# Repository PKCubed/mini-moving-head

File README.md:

# Mini Moving Head

This project aims to create a miniature moving head light fixture for my miniature stage. This fixture needs to have motorized pan and tilt, and should have a bright LED with a collimating lens to create as tight of a beam as possible. For now, a single color LED is acceptable due to the size constraints, as a multicolor LED with individual separate LED dies in side the package causes individual colored beams preventing color mixing.

This project consists of a custom circuit board with an RP2040 on board to take in unbalanced "DMX" signals from the "DMX" bus and read channel data for it's pan and tilt position and the brightness of it's LED. The circuit board drives two 9 gram servos with PWM to give pan and tilt and a constant current driver with PWM control for the LED. We'll need to make sure that the PWM is fast enough that it's not going to cause artifacts on cameras under any circumstances.

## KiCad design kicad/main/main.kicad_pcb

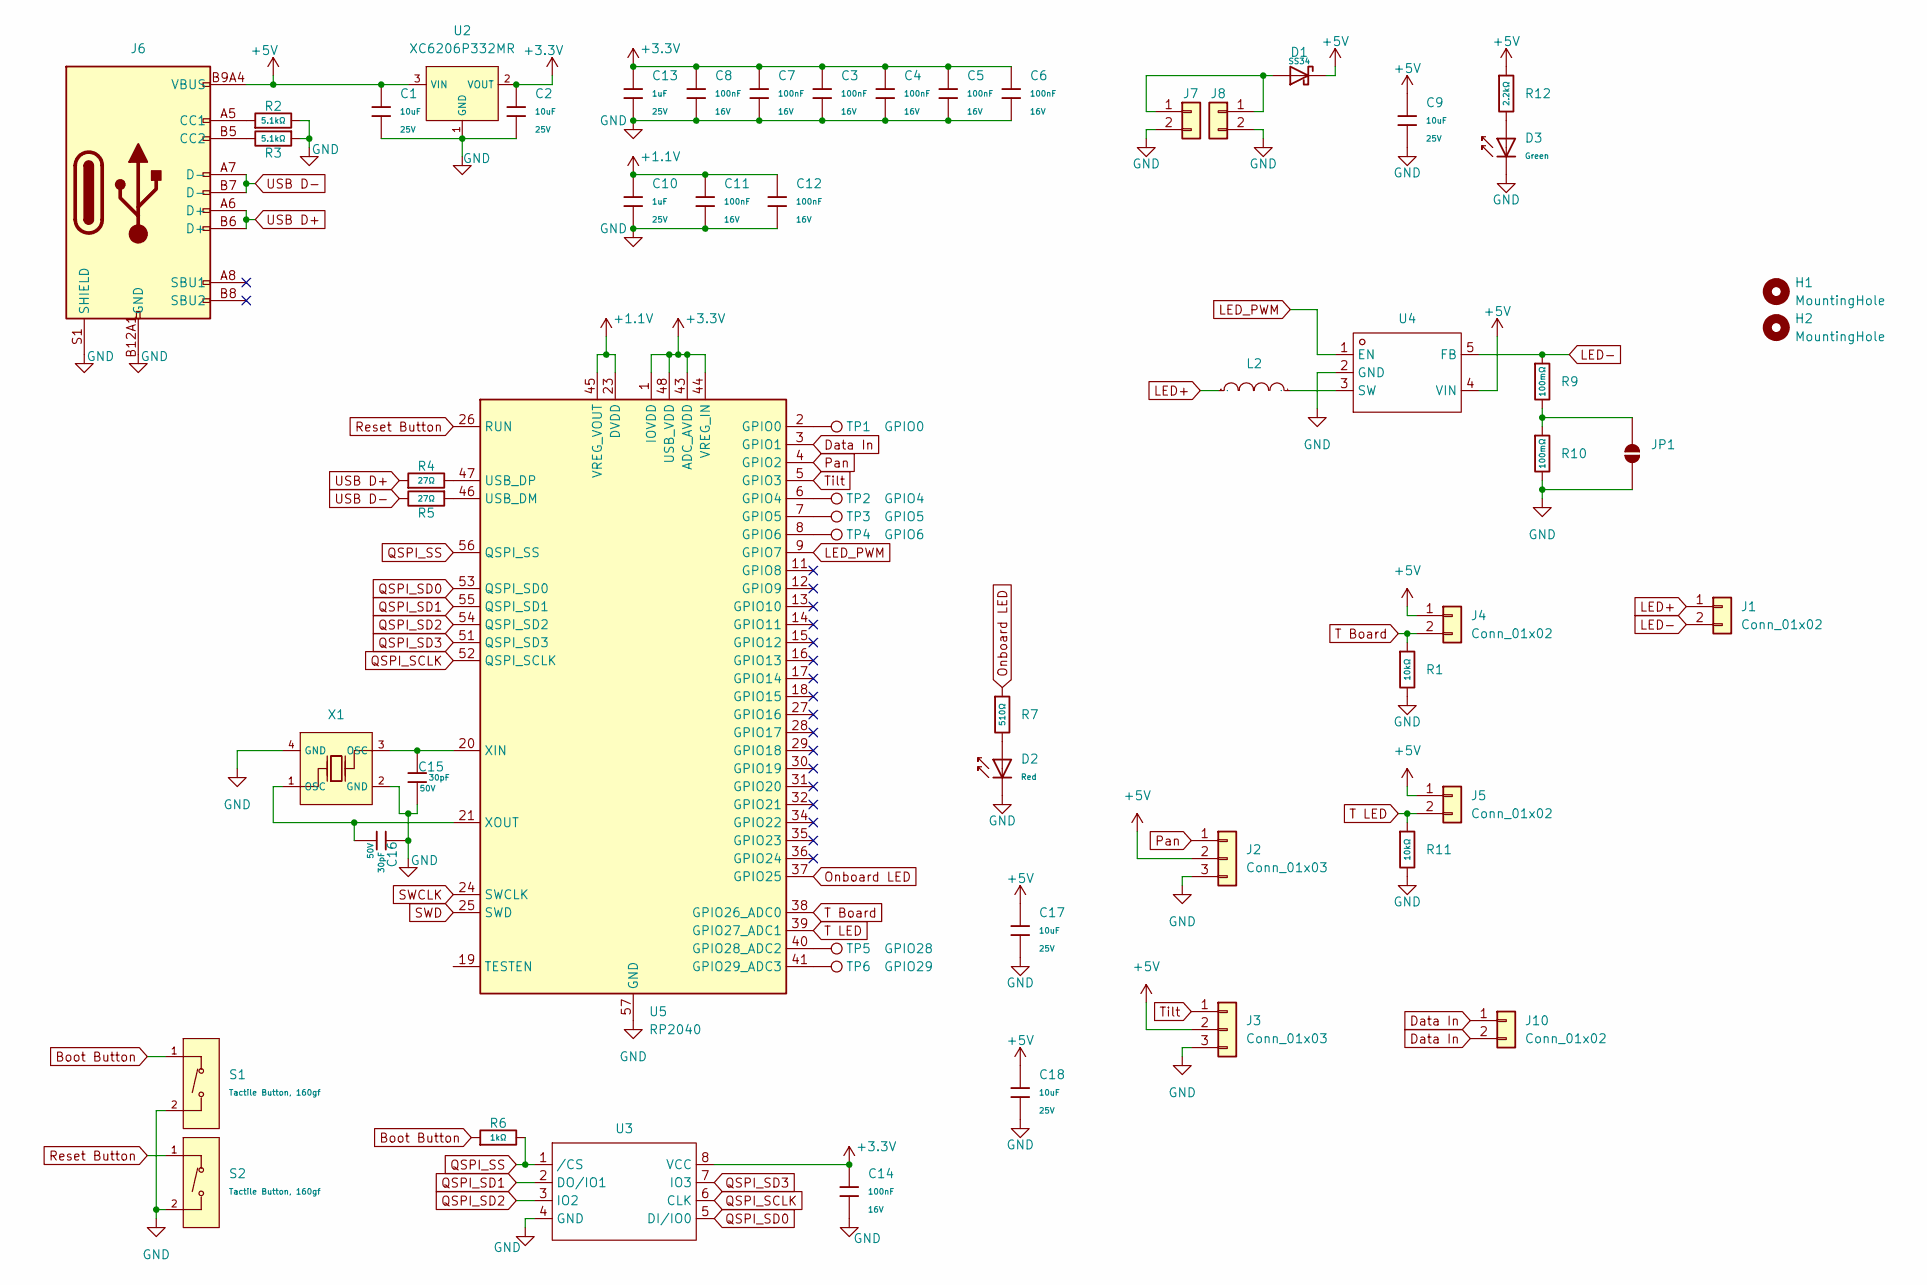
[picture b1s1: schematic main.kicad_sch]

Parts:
C1, C2, C9, C17, C18: 10uF; C_0805; Voltage Rated 25V; Tolerance ±10%; Part CL21A106KAYNNNE; LCSC C15850
C3, C4, C5, C6, C7, C8, C11, C12, C14: 100nF; C_0402; Voltage Rated 16V; Tolerance ±10%; Part CL05B104KO5NNNC; LCSC C1525
C10, C13: 1uF; C_0402; Voltage Rated 25V; Tolerance ±10%; Part CL05A105KA5NQNC; LCSC C52923
C15, C16: 30pF; C_0402; Voltage Rated 50V; Tolerance ±5%; Part 0402CG300J500NT; LCSC C1570
D1: SS34; D_SMA; Forward Voltage (Vf@If) 550mV@3A; Reverse Voltage (Vr) 40V; Part SS34; LCSC C8678
D2: Red; D_0603; Part KT-0603R; LCSC C2286
D3: Green; D_0805; Part KT-0805G; LCSC C2297
H1, H2: MountingHole; MountingHole_2.5mm
J1, J7, J8, J10: Conn_01x02; 2-position
J2, J3: Conn_01x03; 3-position
J4, J5: Conn_01x02; PinHeader_1x02_P2.54mm_Vertical
J6: Connector, USB-TYPE-C-16P; TYPE-C-SMD_HX-TYPE-C-16PIN; LCSC C2927039
JP1: SolderJumper_2_Open; SolderJumper-2_P1.3mm_Open_Pad1.0x1.5mm
L2: 4.7uH; IND-SMD_L3.5-W3.0; Manufacturer Part SM3521-4R7MT; LCSC Part Name 4.7uH ±20% 1.6A
R1, R11: 10kΩ; R_0402; Overload Voltage (Max) 50V; Tolerance ±1%; Part 0402WGF1002TCE; LCSC C25744
R2, R3: 5.1kΩ; R_0402; Overload Voltage (Max) 50V; Tolerance ±1%; Part 0402WGF5101TCE; LCSC C25905
R4, R5: 27Ω; R_0603; Overload Voltage (Max) 75V; Tolerance ±1%; Part 0603WAF270JT5E; LCSC C25190
R6: 1kΩ; R_0402; Overload Voltage (Max) 50V; Tolerance ±1%; Part 0402WGF1001TCE; LCSC C11702
R7: 510Ω; R_0402; Overload Voltage (Max) 50V; Tolerance ±1%; Part 0402WGF5100TCE; LCSC C25123
R9, R10: 100mΩ; R_1206; Overload Voltage (Max) 200V; Tolerance ±1%; Part 1206W4F100LT5E; LCSC C25334
R12: 2.2kΩ; R_0402; Overload Voltage (Max) 50V; Tolerance ±1%; Part 0402WGF2201TCE; LCSC C25879
S1, S2: Tactile Button, 160gf; SW_TS-1088-AR02016; Voltage Rating (Dc) 12V; Part TS-1088-AR02016; LCSC C720477
TP1: GPIO0; TestPoint_Pad_D1.0mm
TP2: GPIO4; TestPoint_Pad_D1.0mm
TP3: GPIO5; TestPoint_Pad_D1.0mm
TP4: GPIO6; TestPoint_Pad_D1.0mm
TP5: GPIO28; TestPoint_Pad_D1.0mm
TP6: GPIO29; TestPoint_Pad_D1.0mm
U2: XC6206P332MR; SOT-23-3_L2.9-W1.6-P1.90-LS2.8-BR; Output Voltage 3.3V; Dropout Voltage 680mV@(100mA); Part XC6206P332MR-G; LCSC C5446
U3: SOIC-8_L5.3-W5.3-P1.27-LS8.0-BL; Manufacturer Part W25Q16JVSSIQ; LCSC Part Name 支持双/四路SPI接口的3V、16Mbit 串行闪存
U4: SOT-23-5_L3.0-W1.7-P0.95-LS2.8-BR; Manufacturer Part PAM2804AAB010; LCSC Part Name 输出1A 降压型驱动
U5: RP2040; QFN-56-1EP_7x7mm_P0.4mm_EP3.2x3.2mm_ThermalVias; LCSC C2040
X1: X322512MSB4SI; CRYSTAL-SMD_4P-L3.2-W2.5-BL; Frequency Tolerance ±10ppm; Part X322512MSB4SI; LCSC C9002

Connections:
+1.1V: C10.1, C11.1, C12.1, U5.23 (DVDD), U5.45 (VREG_VOUT), U5.50 (DVDD)
+3.3V: C2.1, C3.1, C4.1, C5.1, C6.1, C7.1, C8.1, C13.1, C14.2, U2.2 (VOUT), U3.8 (VCC), U5.1 (IOVDD), U5.10 (IOVDD), U5.22 (IOVDD), U5.33 (IOVDD), U5.42 (IOVDD), U5.43 (ADC_AVDD), U5.44 (VREG_IN), U5.48 (USB_VDD), U5.49 (IOVDD)
+5V: C1.1, C9.1, C17.1, C18.1, D1.1, J2.2, J3.2, J4.1, J5.1, J6.A9B4 (VBUS), J6.B9A4 (VBUS), R12.1, U2.3 (VIN), U4.4 (VIN)
Boot Button: R6.1, S1.1 (A)
Data In: J10.1, J10.2, U5.3 (GPIO1)
GND: C1.2, C2.2, C3.2, C4.2, C5.2, C6.2, C7.2, C8.2, C9.2, C10.2, C11.2, C12.2, C13.2, C14.1, C15.2, C16.1, C17.2, C18.2, D2.1, D3.1, J2.3, J3.3, J6.A12B1 (GND), J6.B12A1 (GND), J6.S1 (SHIELD), J7.2, J8.2, JP1.1 (A), R1.2, R2.2, R3.1, R10.2, R11.2, S1.2 (B), S2.2 (B), U2.1 (GND), U3.4 (GND), U4.2 (GND), U5.57 (GND), X1.2 (GND), X1.4 (GND)
LED+: J1.1, L2.1
LED-: J1.2, R9.1, U4.5 (FB)
LED_PWM: U4.1 (EN), U5.9 (GPIO7)
unnamed: D2.2, R7.2
unnamed: D3.2, R12.2
unnamed: J6.A5 (CC1), R2.1
unnamed: J6.B5 (CC2), R3.2
unnamed: D1.2, J7.1, J8.1
unnamed: JP1.2 (B), R9.2, R10.1
unnamed: L2.2, U4.3 (SW)
unnamed: TP1.1 (1_1), U5.2 (GPIO0)
unnamed: TP2.1 (1_1), U5.6 (GPIO4)
unnamed: TP3.1 (1_1), U5.7 (GPIO5)
unnamed: TP4.1 (1_1), U5.8 (GPIO6)
unnamed: TP5.1 (1_1), U5.40 (GPIO28_ADC2)
unnamed: TP6.1 (1_1), U5.41 (GPIO29_ADC3)
unnamed: R5.1, U5.46 (USB_DM)
unnamed: R4.2, U5.47 (USB_DP)
unnamed: C15.1, U5.20 (XIN), X1.3 (OSC)
unnamed: C16.2, U5.21 (XOUT), X1.1 (OSC)
Onboard LED: R7.1, U5.37 (GPIO25)
Pan: J2.1, U5.4 (GPIO2)
QSPI_SCLK: U3.6 (CLK), U5.52 (QSPI_SCLK)
QSPI_SD0: U3.5 (DI/IO0), U5.53 (QSPI_SD0)
QSPI_SD1: U3.2 (DO/IO1), U5.55 (QSPI_SD1)
QSPI_SD2: U3.3 (IO2), U5.54 (QSPI_SD2)
QSPI_SD3: U3.7 (IO3), U5.51 (QSPI_SD3)
QSPI_SS: R6.2, U3.1 (/CS), U5.56 (QSPI_SS)
Reset Button: S2.1 (A), U5.26 (RUN)
SWCLK: U5.24 (SWCLK)
SWD: U5.25 (SWD)
T Board: J4.2, R1.1, U5.38 (GPIO26_ADC0)
T LED: J5.2, R11.1, U5.39 (GPIO27_ADC1)
Tilt: J3.1, U5.5 (GPIO3)
USB D+: J6.A6 (D+), J6.B6 (D+), R4.1
USB D-: J6.A7 (D-), J6.B7 (D-), R5.2

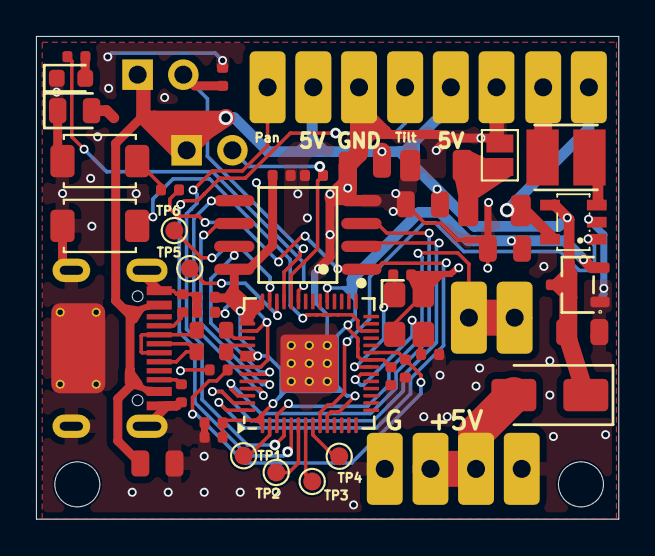
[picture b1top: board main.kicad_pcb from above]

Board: 2 copper layers, 32.4 x 26.8 mm, 54 parts (0 on the bottom side), 39 nets.

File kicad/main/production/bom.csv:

Designator,Footprint,Quantity,Value,LCSC Part #
"C1, C2, C9",C_0805,3,10uF,C15850
"C10, C13",C_0402,2,1uF,C52923
"C11, C12, C3, C4, C5, C6",C_0402,6,100nF,C1525
"C15, C16",C_0402,2,30pF,C1570
D2,D_0603,1,Red,C2286
D3,D_0805,1,Green,C2297
"J1, J10, J7, J8",2-position,4,Conn_01x02,
"J2, J3",3-position,2,Conn_01x03,
"J4, J5",PinHeader_1x02_P2.54mm_Vertical,2,Conn_01x02,
J6,TYPE-C-SMD_HX-TYPE-C-16PIN,1,"Connector, USB-TYPE-C-16P",C2927039
L2,IND-SMD_L3.5-W3.0,1,4.7uH,
"R1, R11",R_0402,2,10kΩ,C25744
"R10, R9",R_1206,2,100mΩ,C25334
"R2, R3",R_0402,2,5.1kΩ,C25905
"R4, R5",R_0603,2,27Ω,C25190
R6,R_0402,1,1kΩ,C11702
R7,R_0402,1,510Ω,C25123
R8,R_0603,1,430Ω,C23170
"S1, S2",SW_TS-1088-AR02016,2,"Tactile Button, 160gf",C720477
TP1,TestPoint_Pad_D1.0mm,1,GPIO0,
TP2,TestPoint_Pad_D1.0mm,1,GPIO4,
TP3,TestPoint_Pad_D1.0mm,1,GPIO5,
TP4,TestPoint_Pad_D1.0mm,1,GPIO6,
TP5,TestPoint_Pad_D1.0mm,1,GPIO28,
TP6,TestPoint_Pad_D1.0mm,1,GPIO29,
U2,SOT-23-3_L2.9-W1.6-P1.90-LS2.8-BR,1,XC6206P332MR,C5446
U3,SOIC-8_L5.3-W5.3-P1.27-LS8.0-BL,1,~,
U4,SOT-23-5_L3.0-W1.7-P0.95-LS2.8-BR,1,~,
U5,QFN-56-1EP_7x7mm_P0.4mm_EP3.2x3.2mm_ThermalVias,1,RP2040,C2040
X1,CRYSTAL-SMD_4P-L3.2-W2.5-BL,1,X322512MSB4SI,C9002

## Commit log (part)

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2026-06-22 Initial kicad files
2026-06-24 Started working on CC regulators
